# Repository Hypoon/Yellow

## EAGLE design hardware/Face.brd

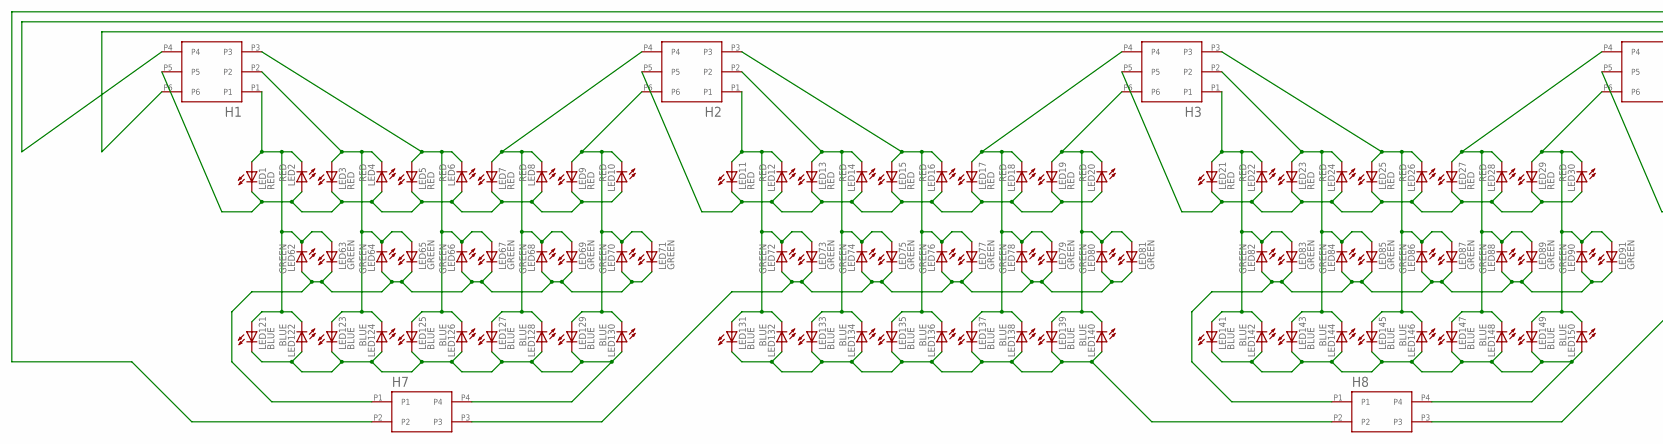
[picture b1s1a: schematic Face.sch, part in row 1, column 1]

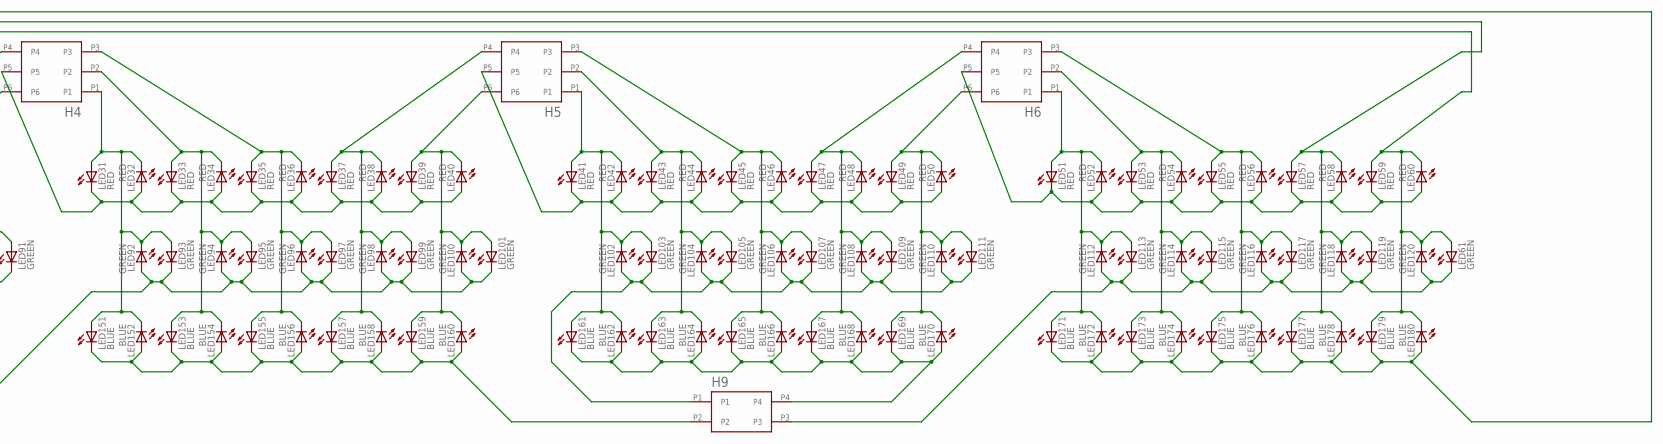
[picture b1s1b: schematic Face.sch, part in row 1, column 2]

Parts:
H1, H2, H3, H4, H5, H6: 2X3; 3X2_1MM_SMD
H7, H8, H9: 2X2; 2X2_1MM_SMD
LED1, LED2, LED3, LED4, LED5, LED6, LED7, LED8, LED9, LED10, LED11, LED12, LED13, LED14, LED15, LED16, LED17, LED18, LED19, LED20, LED21, LED22, LED23, LED24, LED25, LED26, LED27, LED28, LED29, LED30, LED31, LED32, LED33, LED34, LED35, LED36, LED37, LED38, LED39, LED40, LED41, LED42, LED43, LED44, LED45, LED46, LED47, LED48, LED49, LED50, LED51, LED52, LED53, LED54, LED55, LED56, LED57, LED58, LED59, LED60: RED; LED-0603
LED61, LED62, LED63, LED64, LED65, LED66, LED67, LED68, LED69, LED70, LED71, LED72, LED73, LED74, LED75, LED76, LED77, LED78, LED79, LED80, LED81, LED82, LED83, LED84, LED85, LED86, LED87, LED88, LED89, LED90, LED91, LED92, LED93, LED94, LED95, LED96, LED97, LED98, LED99, LED100, LED101, LED102, LED103, LED104, LED105, LED106, LED107, LED108, LED109, LED110, LED111, LED112, LED113, LED114, LED115, LED116, LED117, LED118, LED119, LED120: GREEN; LED-0603
LED121, LED122, LED123, LED124, LED125, LED126, LED127, LED128, LED129, LED130, LED131, LED132, LED133, LED134, LED135, LED136, LED137, LED138, LED139, LED140, LED141, LED142, LED143, LED144, LED145, LED146, LED147, LED148, LED149, LED150, LED151, LED152, LED153, LED154, LED155, LED156, LED157, LED158, LED159, LED160, LED161, LED162, LED163, LED164, LED165, LED166, LED167, LED168, LED169, LED170, LED171, LED172, LED173, LED174, LED175, LED176, LED177, LED178, LED179, LED180: BLUE; LED-0603

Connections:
unnamed: H1.P1, LED1.A, LED2.C, LED62.C, LED63.A, LED121.A, LED122.C
unnamed: H1.P2, LED3.A, LED4.C, LED64.C, LED65.A, LED123.A, LED124.C
unnamed: H1.P3, LED5.A, LED6.C, LED66.C, LED67.A, LED125.A, LED126.C
unnamed: H2.P4, LED7.A, LED8.C, LED68.C, LED69.A, LED127.A, LED128.C
unnamed: H2.P6, LED9.A, LED10.C, LED70.C, LED71.A, LED129.A, LED130.C
unnamed: H2.P1, LED11.A, LED12.C, LED72.C, LED73.A, LED131.A, LED132.C
unnamed: H2.P2, LED13.A, LED14.C, LED74.C, LED75.A, LED133.A, LED134.C
unnamed: H2.P3, LED15.A, LED16.C, LED76.C, LED77.A, LED135.A, LED136.C
unnamed: H3.P4, LED17.A, LED18.C, LED78.C, LED79.A, LED137.A, LED138.C
unnamed: H3.P6, LED19.A, LED20.C, LED80.C, LED81.A, LED139.A, LED140.C
unnamed: H3.P1, LED21.A, LED22.C, LED82.C, LED83.A, LED141.A, LED142.C
unnamed: H3.P2, LED23.A, LED24.C, LED84.C, LED85.A, LED143.A, LED144.C
unnamed: H3.P3, LED25.A, LED26.C, LED86.C, LED87.A, LED145.A, LED146.C
unnamed: H4.P4, LED27.A, LED28.C, LED88.C, LED89.A, LED147.A, LED148.C
unnamed: H4.P6, LED29.A, LED30.C, LED90.C, LED91.A, LED149.A, LED150.C
unnamed: H4.P1, LED31.A, LED32.C, LED92.C, LED93.A, LED151.A, LED152.C
unnamed: H4.P2, LED33.A, LED34.C, LED94.C, LED95.A, LED153.A, LED154.C
unnamed: H4.P3, LED35.A, LED36.C, LED96.C, LED97.A, LED155.A, LED156.C
unnamed: H5.P4, LED37.A, LED38.C, LED98.C, LED99.A, LED157.A, LED158.C
unnamed: H5.P6, LED39.A, LED40.C, LED100.C, LED101.A, LED159.A, LED160.C
unnamed: H5.P1, LED41.A, LED42.C, LED102.C, LED103.A, LED161.A, LED162.C
unnamed: H5.P2, LED43.A, LED44.C, LED104.C, LED105.A, LED163.A, LED164.C
unnamed: H5.P3, LED45.A, LED46.C, LED106.C, LED107.A, LED165.A, LED166.C
unnamed: H6.P4, LED47.A, LED48.C, LED108.C, LED109.A, LED167.A, LED168.C
unnamed: H6.P6, LED49.A, LED50.C, LED110.C, LED111.A, LED169.A, LED170.C
unnamed: H6.P1, LED51.A, LED52.C, LED112.C, LED113.A, LED171.A, LED172.C
unnamed: H6.P2, LED53.A, LED54.C, LED114.C, LED115.A, LED173.A, LED174.C
unnamed: H6.P3, LED55.A, LED56.C, LED116.C, LED117.A, LED175.A, LED176.C
unnamed: H1.P4, LED57.A, LED58.C, LED118.C, LED119.A, LED177.A, LED178.C
unnamed: H1.P6, LED59.A, LED60.C, LED61.A, LED120.C, LED179.A, LED180.C
unnamed: H7.P4, LED121.C, LED122.A, LED123.C, LED124.A, LED125.C, LED126.A, LED127.C, LED128.A, LED129.C, LED130.A
unnamed: H1.P5, LED1.C, LED2.A, LED3.C, LED4.A, LED5.C, LED6.A, LED7.C, LED8.A, LED9.C, LED10.A
unnamed: H2.P5, LED11.C, LED12.A, LED13.C, LED14.A, LED15.C, LED16.A, LED17.C, LED18.A, LED19.C, LED20.A
unnamed: H3.P5, LED21.C, LED22.A, LED23.C, LED24.A, LED25.C, LED26.A, LED27.C, LED28.A, LED29.C, LED30.A
unnamed: H4.P5, LED31.C, LED32.A, LED33.C, LED34.A, LED35.C, LED36.A, LED37.C, LED38.A, LED39.C, LED40.A
unnamed: H5.P5, LED41.C, LED42.A, LED43.C, LED44.A, LED45.C, LED46.A, LED47.C, LED48.A, LED49.C, LED50.A
unnamed: H6.P5, LED51.C, LED52.A, LED53.C, LED54.A, LED55.C, LED56.A, LED57.C, LED58.A, LED59.C, LED60.A
unnamed: H7.P1, LED62.A, LED63.C, LED64.A, LED65.C, LED66.A, LED67.C, LED68.A, LED69.C, LED70.A, LED71.C
unnamed: H7.P3, LED72.A, LED73.C, LED74.A, LED75.C, LED76.A, LED77.C, LED78.A, LED79.C, LED80.A, LED81.C
unnamed: H8.P1, LED82.A, LED83.C, LED84.A, LED85.C, LED86.A, LED87.C, LED88.A, LED89.C, LED90.A, LED91.C
unnamed: H8.P3, LED92.A, LED93.C, LED94.A, LED95.C, LED96.A, LED97.C, LED98.A, LED99.C, LED100.A, LED101.C
unnamed: H9.P1, LED102.A, LED103.C, LED104.A, LED105.C, LED106.A, LED107.C, LED108.A, LED109.C, LED110.A, LED111.C
unnamed: H9.P3, LED61.C, LED112.A, LED113.C, LED114.A, LED115.C, LED116.A, LED117.C, LED118.A, LED119.C, LED120.A
unnamed: H8.P2, LED131.C, LED132.A, LED133.C, LED134.A, LED135.C, LED136.A, LED137.C, LED138.A, LED139.C, LED140.A
unnamed: H8.P4, LED141.C, LED142.A, LED143.C, LED144.A, LED145.C, LED146.A, LED147.C, LED148.A, LED149.C, LED150.A
unnamed: H9.P2, LED151.C, LED152.A, LED153.C, LED154.A, LED155.C, LED156.A, LED157.C, LED158.A, LED159.C, LED160.A
unnamed: H9.P4, LED161.C, LED162.A, LED163.C, LED164.A, LED165.C, LED166.A, LED167.C, LED168.A, LED169.C, LED170.A
unnamed: H7.P2, LED171.C, LED172.A, LED173.C, LED174.A, LED175.C, LED176.A, LED177.C, LED178.A, LED179.C, LED180.A

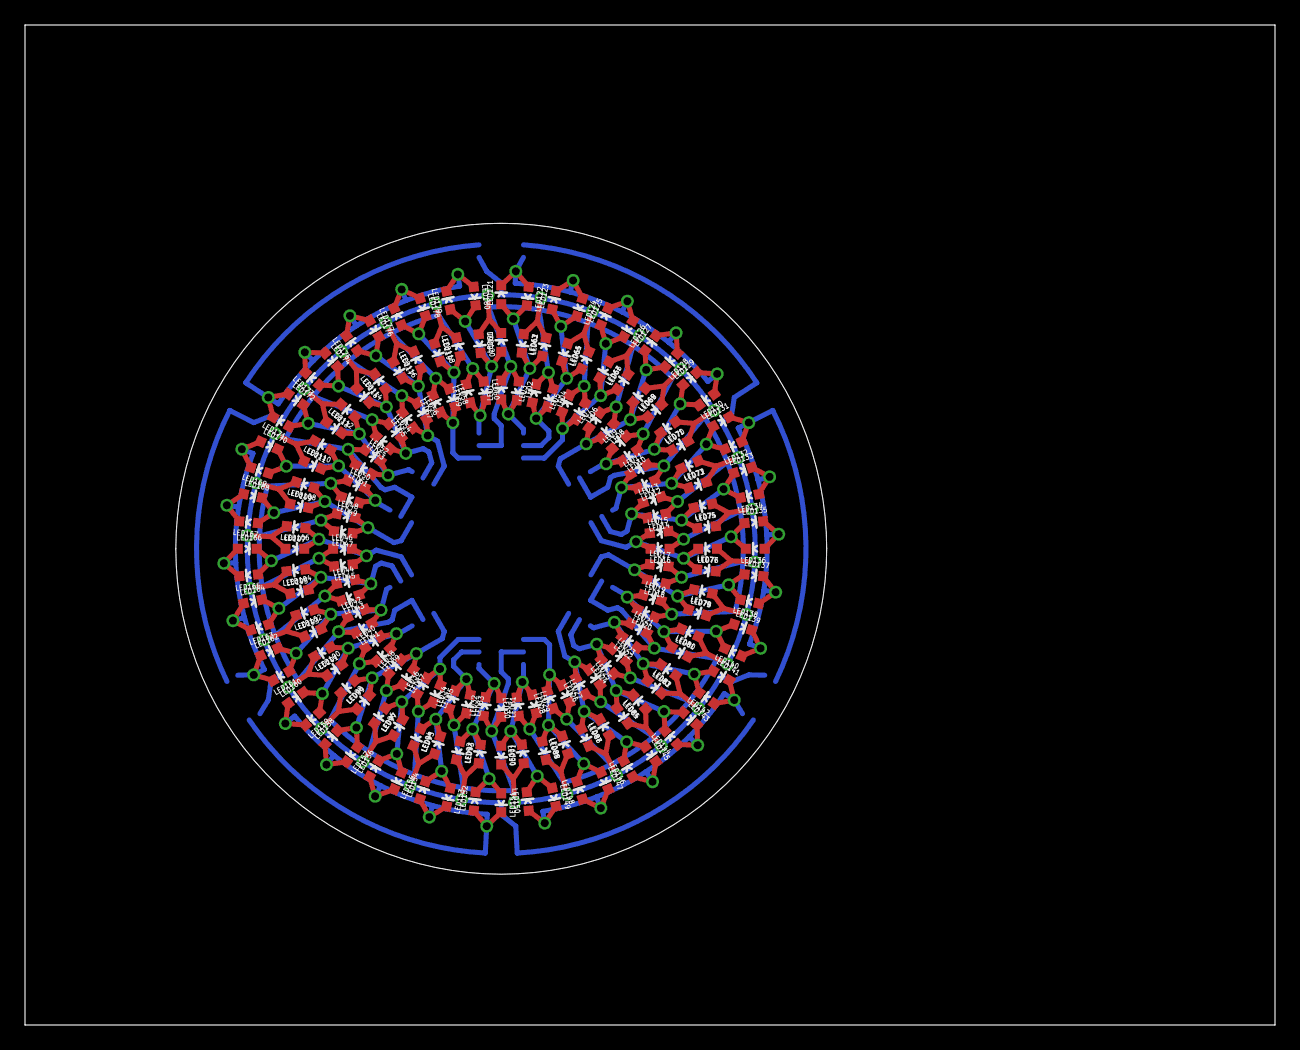
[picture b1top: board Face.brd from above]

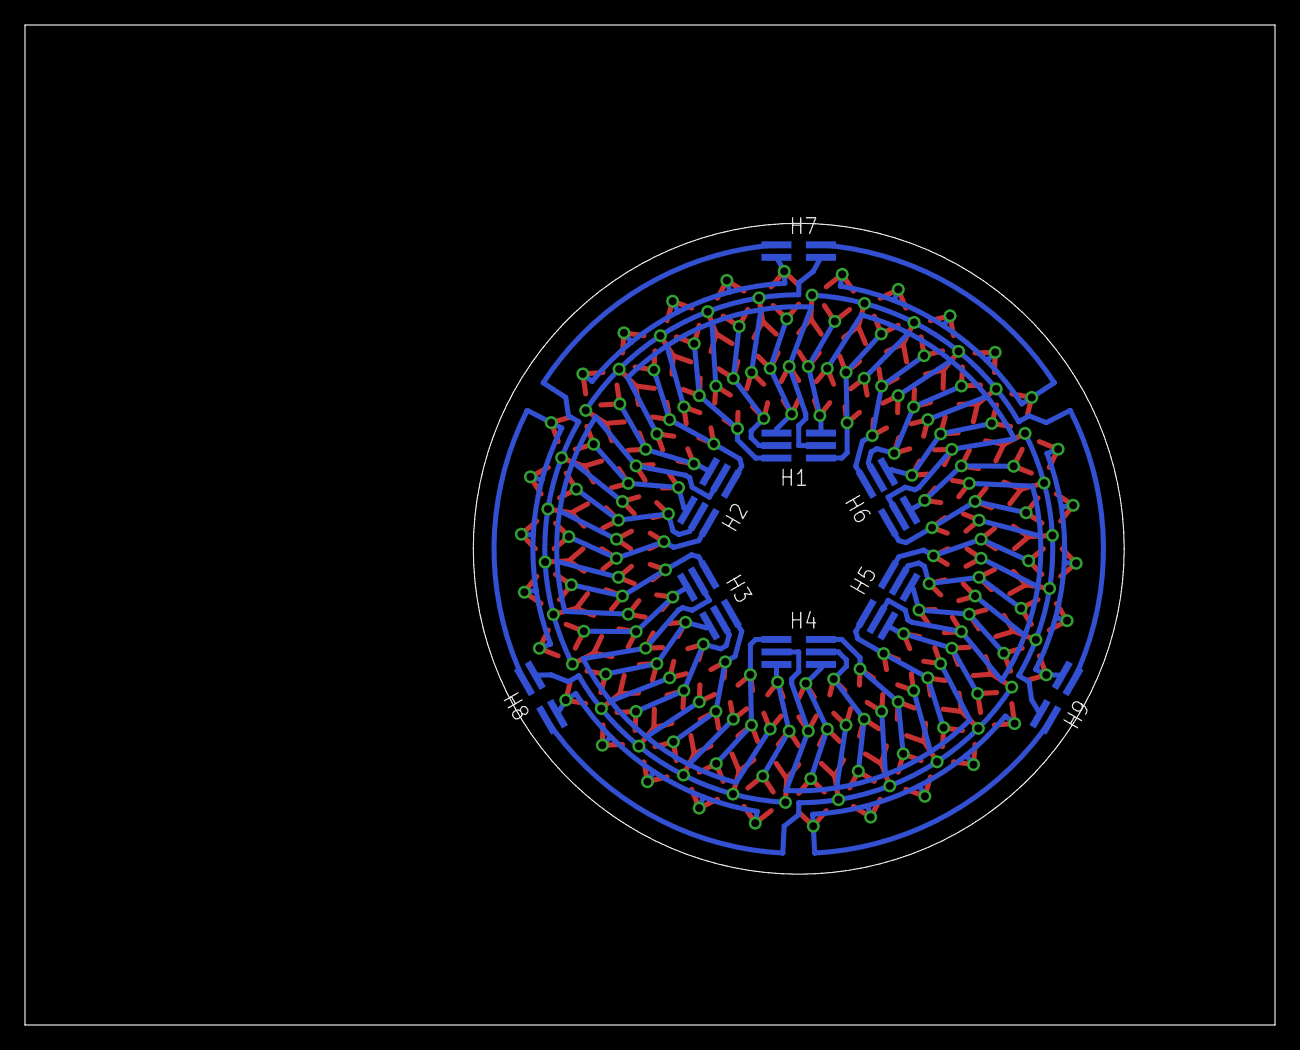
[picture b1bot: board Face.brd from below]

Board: 2 copper layers, 100.0 x 80.0 mm, 189 parts (9 on the bottom side), 48 nets.

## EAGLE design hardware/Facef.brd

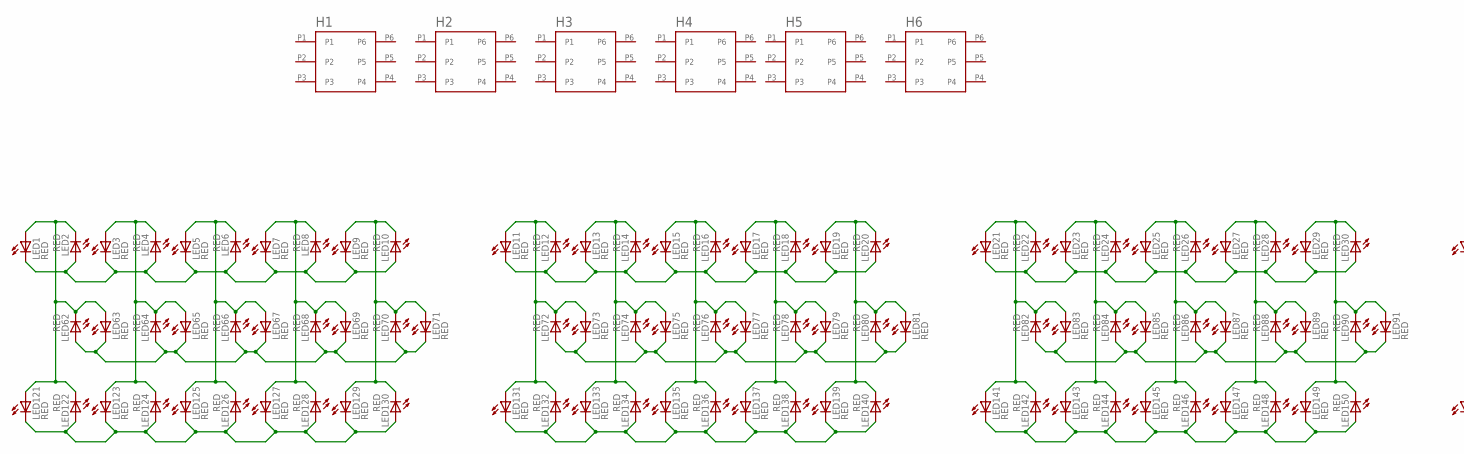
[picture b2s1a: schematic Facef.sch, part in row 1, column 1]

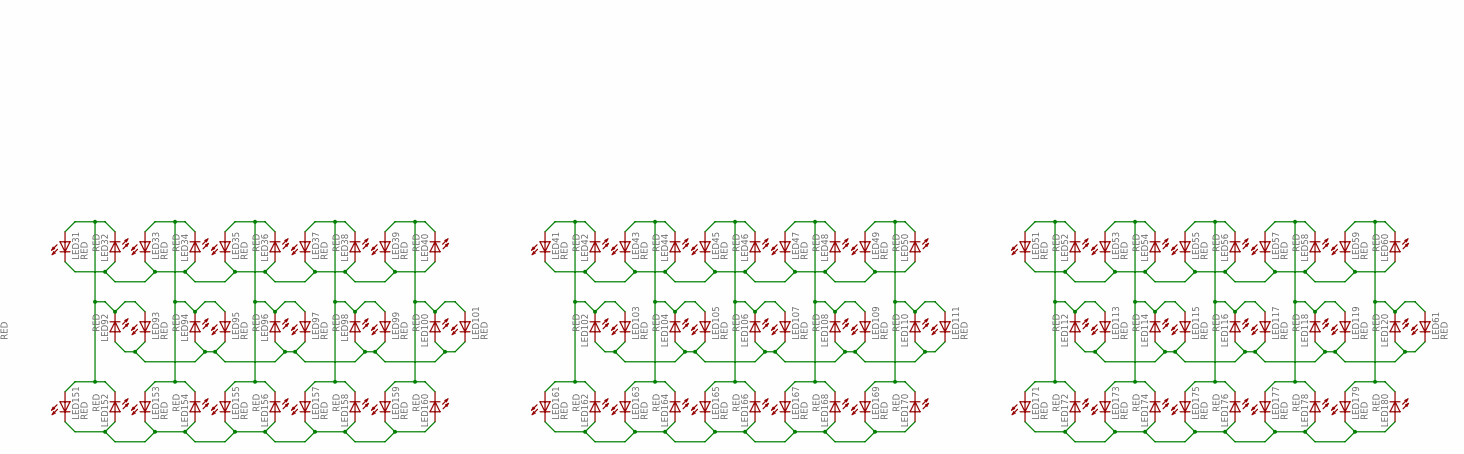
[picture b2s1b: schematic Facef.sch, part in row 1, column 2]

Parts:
H1, H2, H3, H4, H5, H6: 2X3; 3X2_1MM_SMD
LED1, LED2, LED3, LED4, LED5, LED6, LED7, LED8, LED9, LED10, LED11, LED12, LED13, LED14, LED15, LED16, LED17, LED18, LED19, LED20, LED21, LED22, LED23, LED24, LED25, LED26, LED27, LED28, LED29, LED30, LED31, LED32, LED33, LED34, LED35, LED36, LED37, LED38, LED39, LED40, LED41, LED42, LED43, LED44, LED45, LED46, LED47, LED48, LED49, LED50, LED51, LED52, LED53, LED54, LED55, LED56, LED57, LED58, LED59, LED60, LED61, LED62, LED63, LED64, LED65, LED66, LED67, LED68, LED69, LED70, LED71, LED72, LED73, LED74, LED75, LED76, LED77, LED78, LED79, LED80, LED81, LED82, LED83, LED84, LED85, LED86, LED87, LED88, LED89, LED90, LED91, LED92, LED93, LED94, LED95, LED96, LED97, LED98, LED99, LED100, LED101, LED102, LED103, LED104, LED105, LED106, LED107, LED108, LED109, LED110, LED111, LED112, LED113, LED114, LED115, LED116, LED117, LED118, LED119, LED120, LED121, LED122, LED123, LED124, LED125, LED126, LED127, LED128, LED129, LED130, LED131, LED132, LED133, LED134, LED135, LED136, LED137, LED138, LED139, LED140, LED141, LED142, LED143, LED144, LED145, LED146, LED147, LED148, LED149, LED150, LED151, LED152, LED153, LED154, LED155, LED156, LED157, LED158, LED159, LED160, LED161, LED162, LED163, LED164, LED165, LED166, LED167, LED168, LED169, LED170, LED171, LED172, LED173, LED174, LED175, LED176, LED177, LED178, LED179, LED180: RED; LED-0603

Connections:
unnamed: LED1.A, LED2.C, LED62.C, LED63.A, LED121.A, LED122.C
unnamed: LED3.A, LED4.C, LED64.C, LED65.A, LED123.A, LED124.C
unnamed: LED5.A, LED6.C, LED66.C, LED67.A, LED125.A, LED126.C
unnamed: LED7.A, LED8.C, LED68.C, LED69.A, LED127.A, LED128.C
unnamed: LED9.A, LED10.C, LED70.C, LED71.A, LED129.A, LED130.C
unnamed: LED11.A, LED12.C, LED72.C, LED73.A, LED131.A, LED132.C
unnamed: LED13.A, LED14.C, LED74.C, LED75.A, LED133.A, LED134.C
unnamed: LED15.A, LED16.C, LED76.C, LED77.A, LED135.A, LED136.C
unnamed: LED17.A, LED18.C, LED78.C, LED79.A, LED137.A, LED138.C
unnamed: LED19.A, LED20.C, LED80.C, LED81.A, LED139.A, LED140.C
unnamed: LED21.A, LED22.C, LED82.C, LED83.A, LED141.A, LED142.C
unnamed: LED23.A, LED24.C, LED84.C, LED85.A, LED143.A, LED144.C
unnamed: LED25.A, LED26.C, LED86.C, LED87.A, LED145.A, LED146.C
unnamed: LED27.A, LED28.C, LED88.C, LED89.A, LED147.A, LED148.C
unnamed: LED29.A, LED30.C, LED90.C, LED91.A, LED149.A, LED150.C
unnamed: LED31.A, LED32.C, LED92.C, LED93.A, LED151.A, LED152.C
unnamed: LED33.A, LED34.C, LED94.C, LED95.A, LED153.A, LED154.C
unnamed: LED35.A, LED36.C, LED96.C, LED97.A, LED155.A, LED156.C
unnamed: LED37.A, LED38.C, LED98.C, LED99.A, LED157.A, LED158.C
unnamed: LED39.A, LED40.C, LED100.C, LED101.A, LED159.A, LED160.C
unnamed: LED41.A, LED42.C, LED102.C, LED103.A, LED161.A, LED162.C
unnamed: LED43.A, LED44.C, LED104.C, LED105.A, LED163.A, LED164.C
unnamed: LED45.A, LED46.C, LED106.C, LED107.A, LED165.A, LED166.C
unnamed: LED47.A, LED48.C, LED108.C, LED109.A, LED167.A, LED168.C
unnamed: LED49.A, LED50.C, LED110.C, LED111.A, LED169.A, LED170.C
unnamed: LED51.A, LED52.C, LED112.C, LED113.A, LED171.A, LED172.C
unnamed: LED53.A, LED54.C, LED114.C, LED115.A, LED173.A, LED174.C
unnamed: LED55.A, LED56.C, LED116.C, LED117.A, LED175.A, LED176.C
unnamed: LED57.A, LED58.C, LED118.C, LED119.A, LED177.A, LED178.C
unnamed: LED59.A, LED60.C, LED61.A, LED120.C, LED179.A, LED180.C
unnamed: LED121.C, LED122.A, LED123.C, LED124.A, LED125.C, LED126.A, LED127.C, LED128.A, LED129.C, LED130.A
unnamed: LED1.C, LED2.A, LED3.C, LED4.A, LED5.C, LED6.A, LED7.C, LED8.A, LED9.C, LED10.A
unnamed: LED11.C, LED12.A, LED13.C, LED14.A, LED15.C, LED16.A, LED17.C, LED18.A, LED19.C, LED20.A
unnamed: LED21.C, LED22.A, LED23.C, LED24.A, LED25.C, LED26.A, LED27.C, LED28.A, LED29.C, LED30.A
unnamed: LED31.C, LED32.A, LED33.C, LED34.A, LED35.C, LED36.A, LED37.C, LED38.A, LED39.C, LED40.A
unnamed: LED41.C, LED42.A, LED43.C, LED44.A, LED45.C, LED46.A, LED47.C, LED48.A, LED49.C, LED50.A
unnamed: LED51.C, LED52.A, LED53.C, LED54.A, LED55.C, LED56.A, LED57.C, LED58.A, LED59.C, LED60.A
unnamed: LED62.A, LED63.C, LED64.A, LED65.C, LED66.A, LED67.C, LED68.A, LED69.C, LED70.A, LED71.C
unnamed: LED72.A, LED73.C, LED74.A, LED75.C, LED76.A, LED77.C, LED78.A, LED79.C, LED80.A, LED81.C
unnamed: LED82.A, LED83.C, LED84.A, LED85.C, LED86.A, LED87.C, LED88.A, LED89.C, LED90.A, LED91.C
unnamed: LED92.A, LED93.C, LED94.A, LED95.C, LED96.A, LED97.C, LED98.A, LED99.C, LED100.A, LED101.C
unnamed: LED102.A, LED103.C, LED104.A, LED105.C, LED106.A, LED107.C, LED108.A, LED109.C, LED110.A, LED111.C
unnamed: LED61.C, LED112.A, LED113.C, LED114.A, LED115.C, LED116.A, LED117.C, LED118.A, LED119.C, LED120.A
unnamed: LED131.C, LED132.A, LED133.C, LED134.A, LED135.C, LED136.A, LED137.C, LED138.A, LED139.C, LED140.A
unnamed: LED141.C, LED142.A, LED143.C, LED144.A, LED145.C, LED146.A, LED147.C, LED148.A, LED149.C, LED150.A
unnamed: LED151.C, LED152.A, LED153.C, LED154.A, LED155.C, LED156.A, LED157.C, LED158.A, LED159.C, LED160.A
unnamed: LED161.C, LED162.A, LED163.C, LED164.A, LED165.C, LED166.A, LED167.C, LED168.A, LED169.C, LED170.A
unnamed: LED171.C, LED172.A, LED173.C, LED174.A, LED175.C, LED176.A, LED177.C, LED178.A, LED179.C, LED180.A

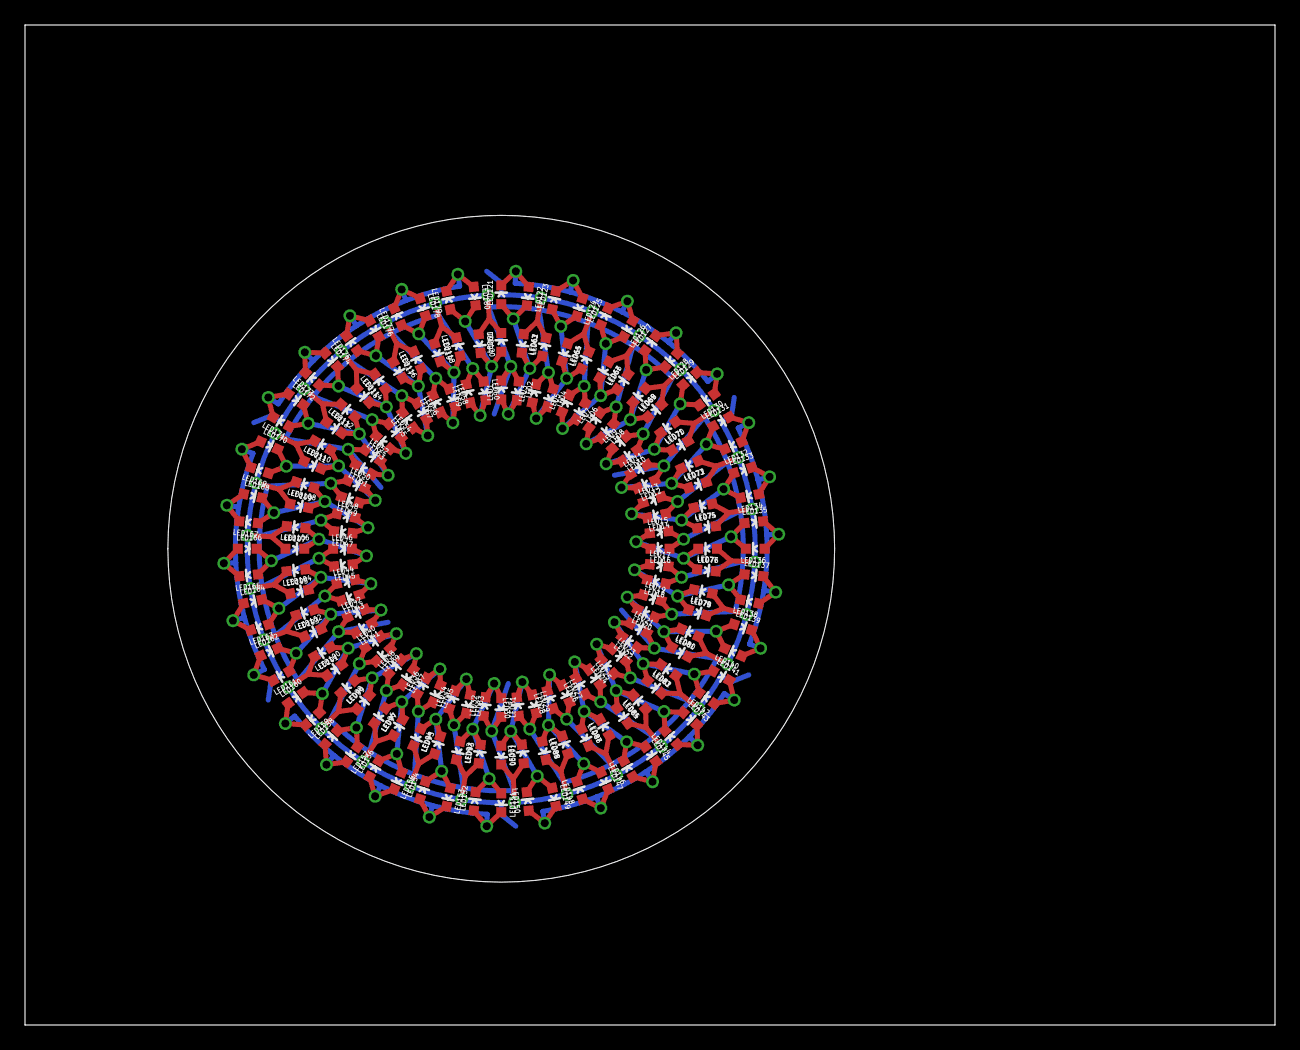
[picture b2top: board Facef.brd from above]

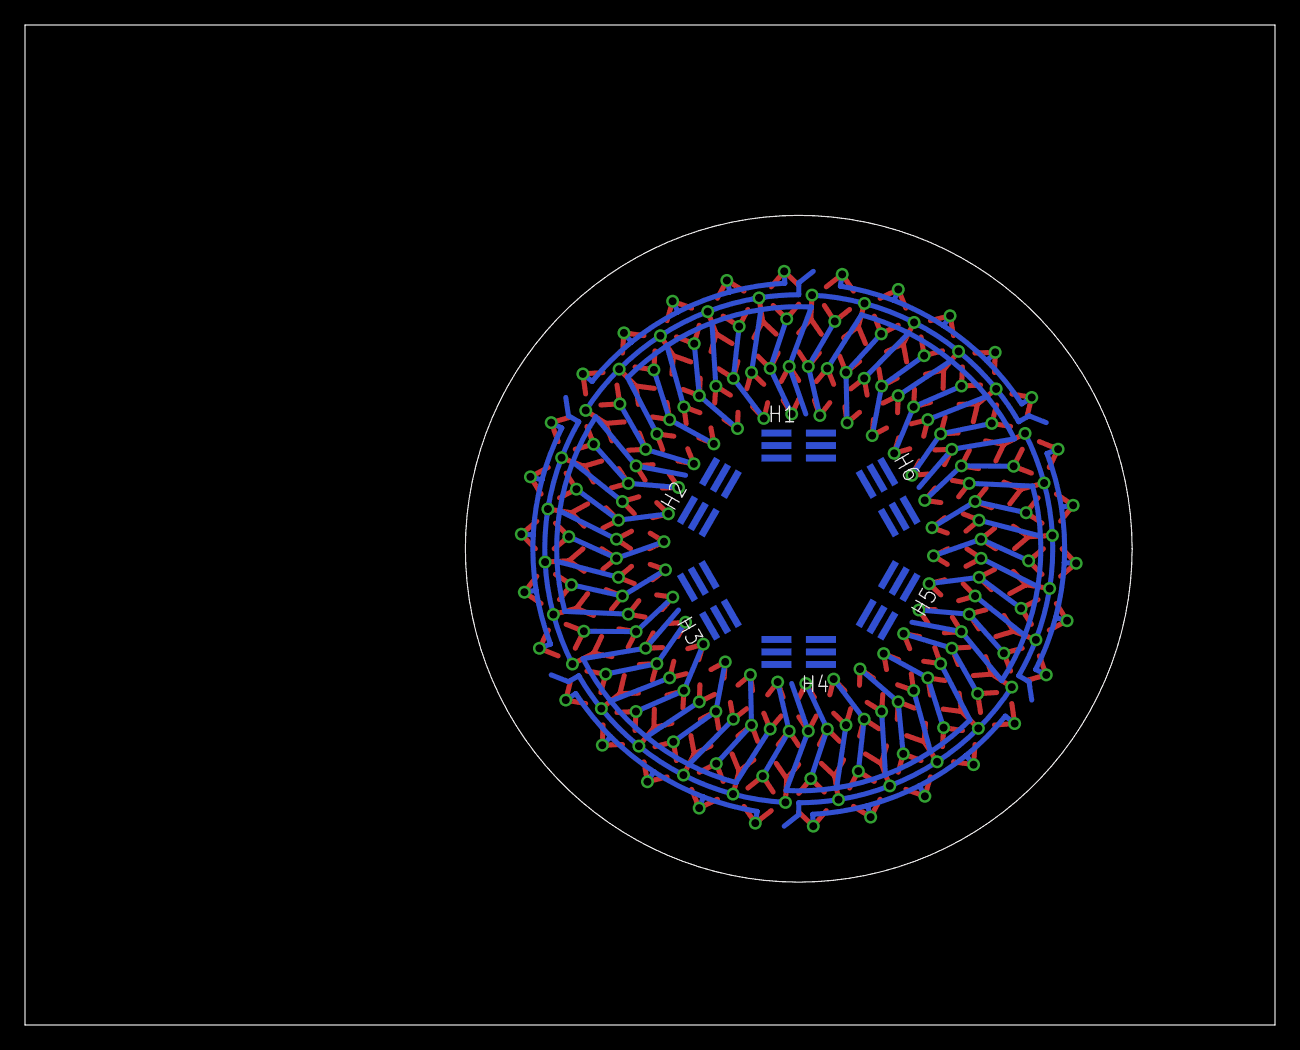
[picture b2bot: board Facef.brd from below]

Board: 2 copper layers, 100.0 x 80.0 mm, 186 parts (6 on the bottom side), 48 nets.

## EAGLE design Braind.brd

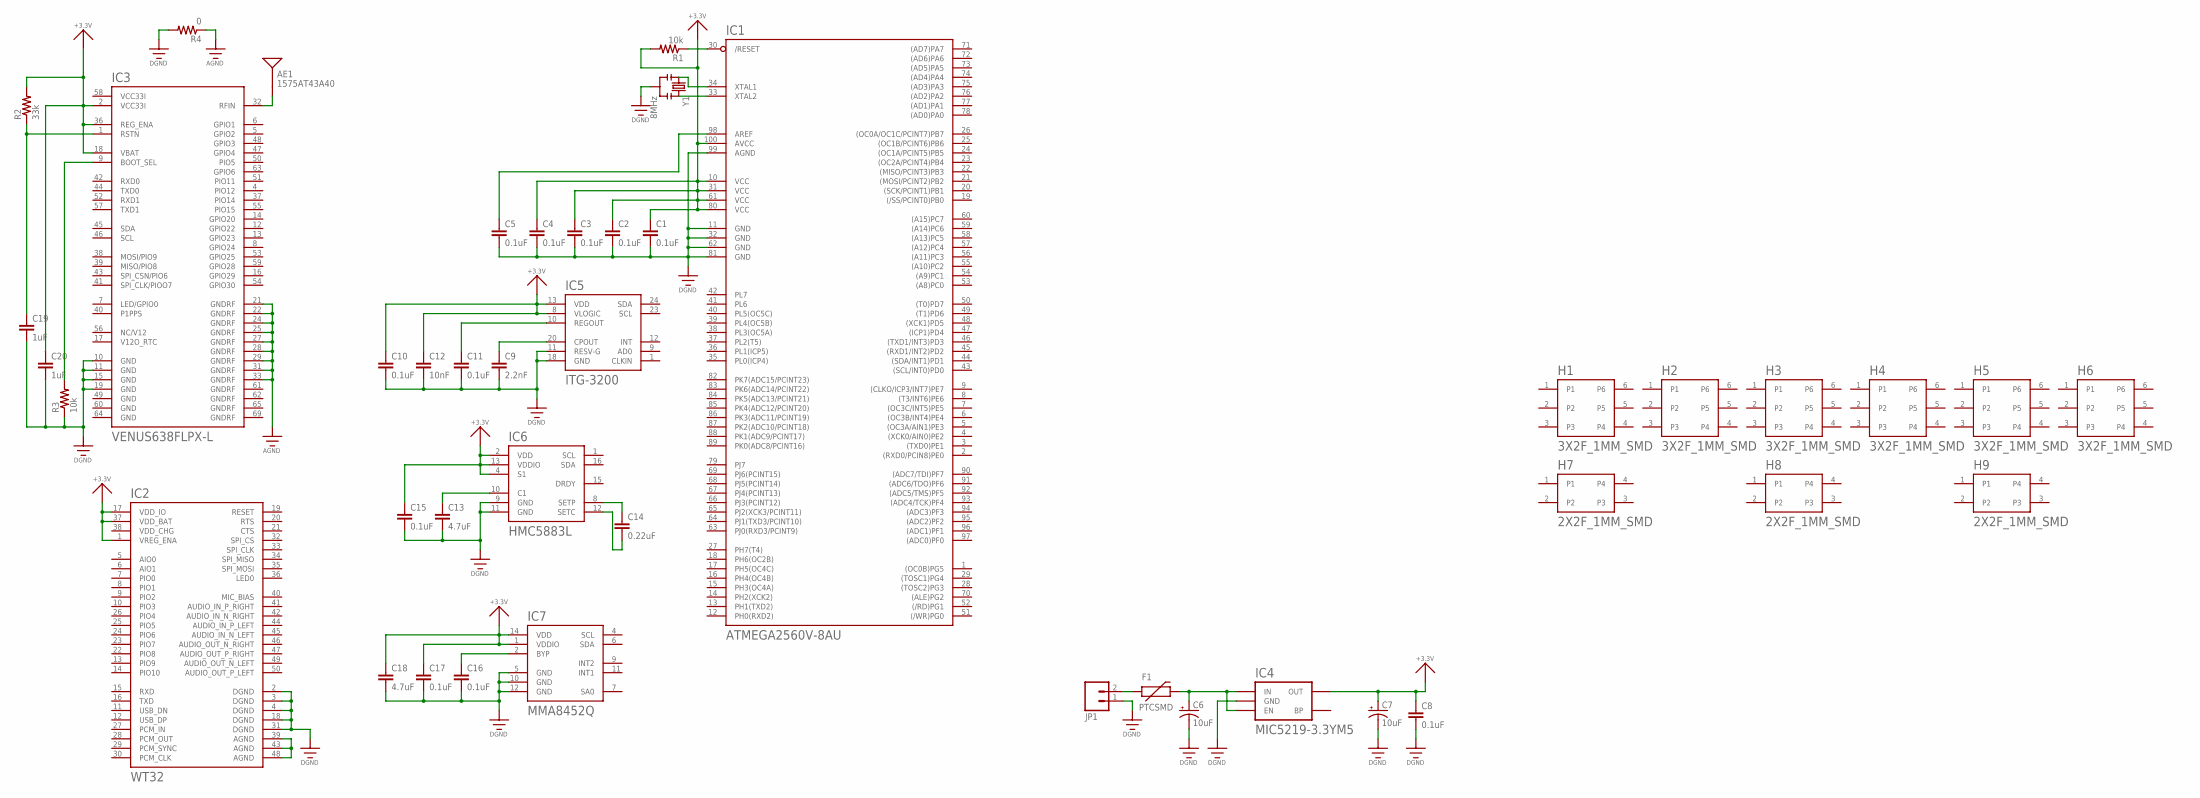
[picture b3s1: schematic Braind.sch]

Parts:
AE1: 1575AT43A40
C1, C2, C3, C4, C5, C8, C10, C11, C15, C16, C17: 0.1uF; 0603-CAP
C6, C7: 10uF; EIA3216
C9: 2.2nF; 0603-CAP
C12: 10nF; 0603-CAP
C13, C18: 4.7uF; 0603-CAP
C14: 0.22uF; 0603-CAP
C19, C20: 1uF; 0603-CAP
F1: PTCSMD; PTC-1206
H1, H2, H3, H4, H5, H6: 3X2F_1MM_SMD
H7, H8, H9: 2X2F_1MM_SMD
IC1: ATMEGA2560V-8AU; TQFP100
IC2: WT32
IC3: VENUS638FLPX-L; VENUS638FLPX
IC4: MIC5219-3.3YM5; SOT23-5
IC5: ITG-3200; QFN-24
IC6: HMC5883L; LPCC-16
IC7: MMA8452Q; QFN-COL-16
JP1: M02-JST-2MM-SMT; JST-2-SMD
R1, R3: 10k; 0603-RES
R2: 33k; 0603-RES
R4: 0; 0603-RES
Y1: 8MHz; RESONATOR-SMD

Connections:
+3.3V: IC2.1 (VREG_ENA), IC2.17 (VDD_IO), IC2.37 (VDD_BAT)
+3V3: C1.1, C2.1, C3.1, C4.1, C7.A (+), C8.1, C10.1, C12.1, C15.1, C17.1, C18.1, C20.1, IC1.10 (VCC), IC1.31 (VCC), IC1.61 (VCC), IC1.80 (VCC), IC1.100 (AVCC), IC3.2 (VCC33I), IC3.18 (VBAT), IC3.36 (REG_ENA), IC4.5 (OUT), IC5.8 (VLOGIC), IC5.13 (VDD), IC6.2 (VDD), IC6.4 (S1), IC6.13 (VDDIO), IC7.1 (VDDIO), IC7.14 (VDD), R1.2, R2.2
AGND: R4.1
DGND: IC2.2 (DGND), IC2.3 (DGND), IC2.4 (DGND), IC2.18 (DGND), IC2.31 (DGND), R4.2
GND: C1.2, C2.2, C3.2, C4.2, C5.2, C6.C (-), C7.C (-), C8.2, C9.2, C10.2, C11.2, C12.2, C13.2, C15.2, C16.2, C17.2, C18.2, C19.2, C20.2, IC1.11 (GND), IC1.32 (GND), IC1.62 (GND), IC1.81 (GND), IC1.99 (AGND), IC3.10 (GND), IC3.11 (GND), IC3.15 (GND), IC3.19 (GND), IC3.21 (GNDRF), IC3.22 (GNDRF), IC3.24 (GNDRF), IC3.25 (GNDRF), IC3.27 (GNDRF), IC3.28 (GNDRF), IC3.29 (GNDRF), IC3.31 (GNDRF), IC3.33 (GNDRF), IC4.2 (GND), IC5.11 (RESV-G), IC5.18 (GND), IC6.9 (GND), IC6.11 (GND), IC7.5 (GND), IC7.10 (GND), IC7.12 (GND), JP1.1 (2), R3.1, Y1.2
unnamed: C5.1, IC1.98 (AREF)
unnamed: IC1.33 (XTAL2), Y1.3
unnamed: IC1.34 (XTAL1), Y1.1
unnamed: F1.1, JP1.2 (1)
unnamed: IC1.30 (/RESET), R1.1
unnamed: C6.A (+), F1.2, IC4.1 (IN), IC4.3 (EN)
unnamed: IC3.9 (BOOT_SEL), R3.2
unnamed: IC2.39 (AGND), IC2.43 (AGND), IC2.48 (AGND)
unnamed: C13.1, IC6.10 (C1)
unnamed: C9.1, IC5.20 (CPOUT)
unnamed: C11.1, IC5.10 (REGOUT)
unnamed: C14.1, IC6.8 (SETP)
unnamed: C14.2, IC6.12 (SETC)
unnamed: C16.1, IC7.2 (BYP)
unnamed: AE1.1, IC3.32 (RFIN)
unnamed: C19.1, IC3.1 (RSTN), R2.1

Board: 2 copper layers, 44 parts (15 on the bottom side), 20 nets, no tracks yet.

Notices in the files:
parts and their libraries:
SparkFun-Passives: Licensing: CC v3.0 Share-Alike You are welcome to use this library for commercial purposes.
